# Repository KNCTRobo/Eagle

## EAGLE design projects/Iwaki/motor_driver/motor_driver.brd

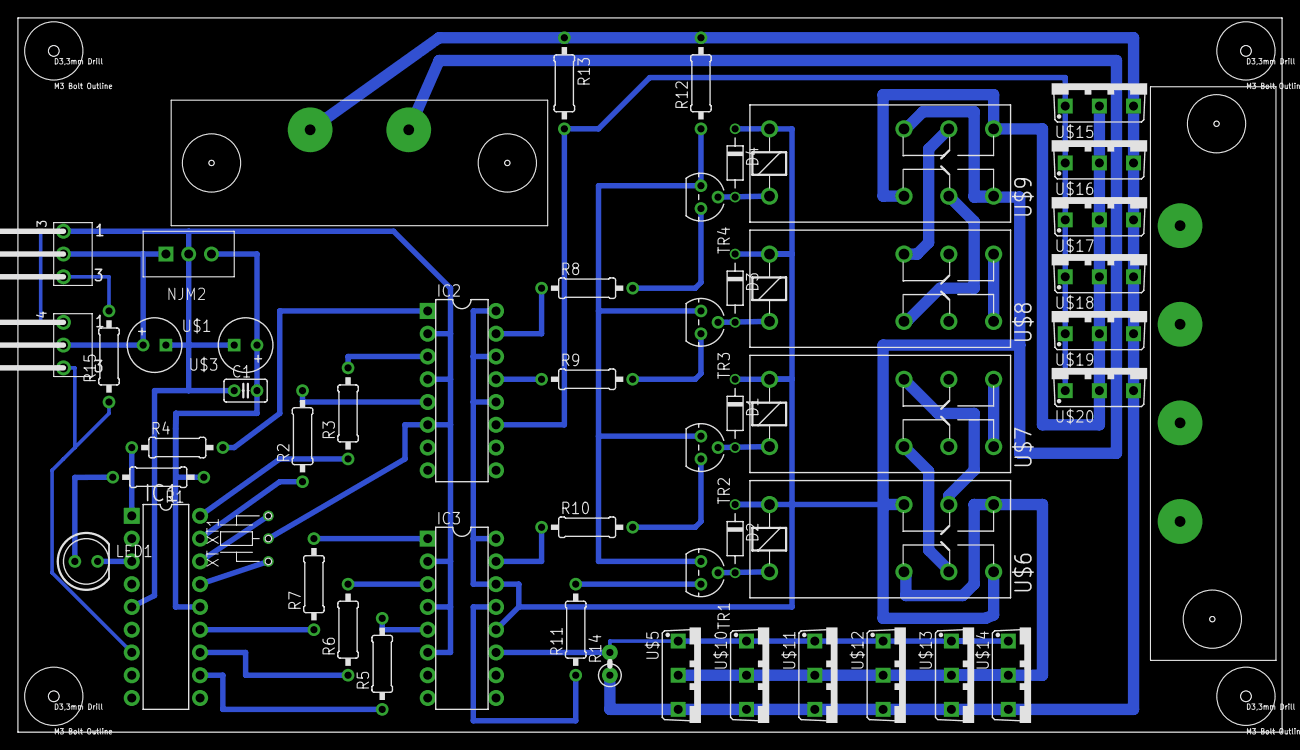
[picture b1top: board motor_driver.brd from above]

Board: 2 copper layers, 141.0 x 79.7 mm, 56 parts (0 on the bottom side), 50 nets.

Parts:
C1: C-2.54
D1, D2, D3, D4: DIODE7.5
H1, H2, H3, H4: HOLE3.3M3BOLT; HOLE3.3
IC1: PIC16F648; DIL18
IC2, IC3: TLP521; DIL16
J3, J4: 3PIN(L); 3PL
LED1: LED5MM
NJM2: NJM7805
R1: 2k; 0207/10
R2, R3, R4, R5, R6, R7, R8, R9, R10, R11: 10k; 0207/10
R12: 1; 0207/10
R13: 510; 0207/10
R14: 510; R0207V
R15: 0207/10
TR1, TR2, TR3, TR4: 2SC2001; TO92BCE
U$1, U$3: C-ELEC; C-6MM
U$2: BP341L
U$4: BP341L_1; BP341L
U$5, U$10, U$11, U$12, U$13, U$14, U$15, U$16, U$17, U$18, U$19, U$20: N-MOS; TO220BV
U$6, U$7, U$8, U$9: RELAY(L); G2R2
XT1: CERALOCK

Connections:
5V: C1.P$2, IC1.14, NJM2.OUT, R1.1, U$3.+
9V: J3.2, J4.2, NJM2.IN, U$1.+
12V: D1.PK, D2.PK, D3.PK, D4.PK, IC2.12, IC2.14, IC2.16, IC3.12, IC3.14, IC3.16, U$4.P$1, U$6.4, U$6.7, U$6.8, U$7.8, U$8.8, U$9.4, U$9.7, U$9.8
FET_D1: U$9.2, U$9.5, U$15.D, U$16.D, U$17.D, U$18.D, U$19.D, U$20.D
FET_G1: IC2.11, R13.2, U$15.G, U$16.G, U$17.G, U$18.G, U$19.G, U$20.G
FET_G2: IC3.11, R14.2, U$5.G, U$10.G, U$11.G, U$12.G, U$13.G, U$14.G
GND1: C1.P$1, IC1.5, IC2.2, IC2.4, IC2.6, IC3.2, IC3.4, IC3.6, J3.1, J4.1, NJM2.GND, U$1.-, U$3.-, XT1.P2
GND2: R12.2, R13.1, R14.1, U$4.P$2, U$5.S, U$10.S, U$11.S, U$12.S, U$13.S, U$14.S, U$15.S, U$16.S, U$17.S, U$18.S, U$19.S, U$20.S
GND3: R12.1, TR1.E, TR2.E, TR3.E, TR4.E
LED_A: LED1.A, R1.2
LED_C: IC1.3, LED1.K
unnamed: IC1.16, XT1.P3
unnamed: J3.3, R15.2
unnamed: IC1.15, XT1.P1
unnamed: IC1.17, R2.1
unnamed: IC1.18, R3.1
unnamed: IC1.1, R4.1
unnamed: IC1.13, R7.1
unnamed: IC1.12, R6.1
unnamed: IC1.11, R5.1
unnamed: IC2.5, R2.2
unnamed: IC2.3, R3.2
unnamed: IC2.1, R4.2
unnamed: IC3.1, R7.2
unnamed: IC3.3, R6.2
unnamed: IC3.5, R5.2
unnamed: IC2.15, R8.1
unnamed: IC2.13, R9.1
unnamed: IC3.15, R10.1
unnamed: IC3.13, R11.1
unnamed: R11.2, TR1.B
unnamed: D4.PA, TR4.C, U$9.1
unnamed: D3.PA, TR3.C, U$8.1
unnamed: D1.PA, TR2.C, U$7.1
unnamed: D2.PA, TR1.C, U$6.1
unnamed: U$2.P3, U$7.6
unnamed: U$5.D, U$6.2, U$6.5, U$10.D, U$11.D, U$12.D, U$13.D, U$14.D
unnamed: U$8.7, U$9.6
unnamed: U$8.2, U$9.3
unnamed: U$8.4, U$8.5
unnamed: R8.2, TR4.B
unnamed: R9.2, TR3.B
unnamed: R10.2, TR2.B
unnamed: U$2.P2, U$8.3
unnamed: U$2.P1, U$8.6
unnamed: U$2.P4, U$7.3
unnamed: U$6.6, U$7.7
unnamed: U$6.3, U$7.2
unnamed: U$7.4, U$7.5
SIGNAL: IC1.7, J4.3, R15.1

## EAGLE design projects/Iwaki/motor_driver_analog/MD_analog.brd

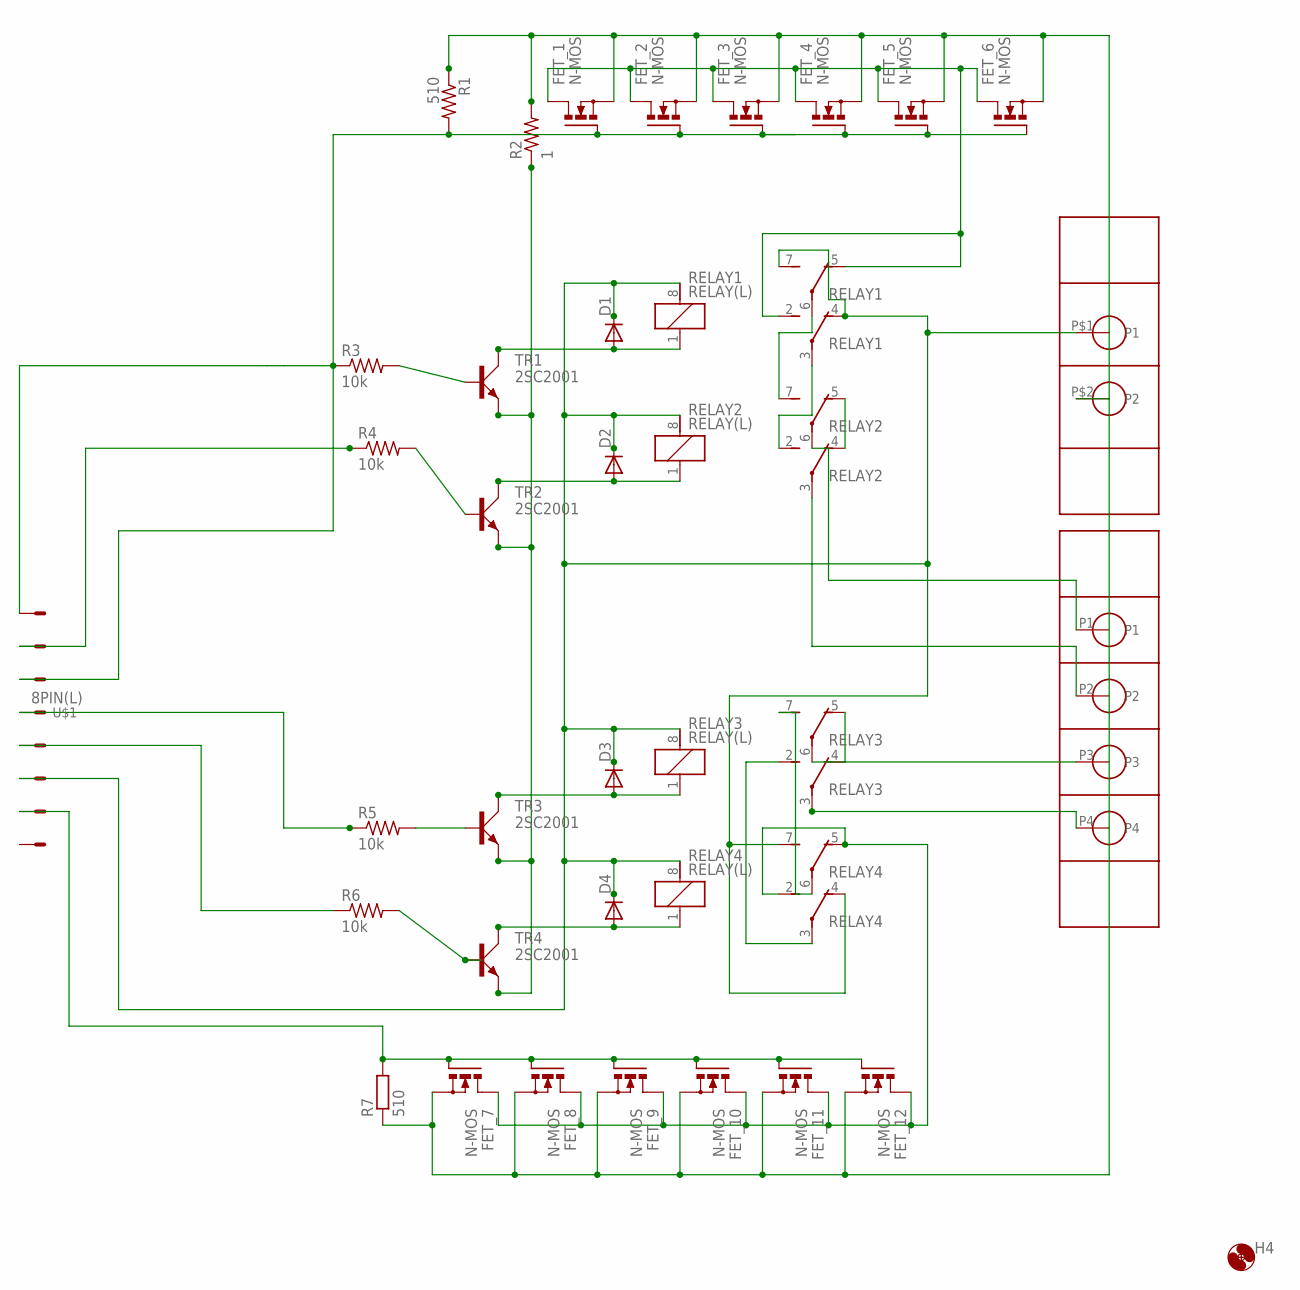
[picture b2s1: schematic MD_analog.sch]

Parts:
D1, D2, D3, D4: DIODE7.5
FET_1, FET_2, FET_3, FET_4, FET_5, FET_6, FET_7, FET_8, FET_9, FET_10, FET_11, FET_12: N-MOS; TO220BV
H4: HOLE3.3M3BOLT; HOLE3.3
R1: 510; 0207/10
R2: 1; 0207/10
R3, R4, R5, R6: 10k; 0207/10
R7: 510; R0207V
RELAY1, RELAY2, RELAY3, RELAY4: RELAY(L); G2R2
TR1, TR2, TR3, TR4: 2SC2001; TO92BCE
U$1: 8PIN(L); 8PL
U$2: BP341L
U$4: BP341L_1; BP341L

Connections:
12V: D1.PK (C), D2.PK (C), D3.PK (C), D4.PK (C), RELAY1.4 (O), RELAY1.7 (S), RELAY1.8 (2), RELAY2.8 (2), RELAY3.8 (2), RELAY4.4 (O), RELAY4.7 (S), RELAY4.8 (2), U$1.P3, U$4.P$1 (P1)
FET_G1: FET_1.G, FET_2.G, FET_3.G, FET_4.G, FET_5.G, FET_6.G, R1.2, U$1.P6
FET_G2: FET_7.G, FET_8.G, FET_9.G, FET_10.G, FET_11.G, FET_12.G, R7.2, U$1.P2
GND2: FET_1.S, FET_2.S, FET_3.S, FET_4.S, FET_5.S, FET_6.S, FET_7.S, FET_8.S, FET_9.S, FET_10.S, FET_11.S, FET_12.S, R1.1, R2.2, R7.1, U$4.P$2 (P2)
GND3: R2.1, TR1.E, TR2.E, TR3.E, TR4.E
MOS_D1: FET_7.D, FET_8.D, FET_9.D, FET_10.D, FET_11.D, FET_12.D, RELAY4.2 (S), RELAY4.5 (O)
MOS_D2: FET_1.D, FET_2.D, FET_3.D, FET_4.D, FET_5.D, FET_6.D, RELAY1.2 (S), RELAY1.5 (O)
unnamed: R3.1, U$1.P8
unnamed: R4.1, U$1.P7
unnamed: R5.1, U$1.P5
unnamed: R6.1, U$1.P4
unnamed: R6.2, TR4.B
unnamed: D1.PA (A), RELAY1.1, TR1.C
unnamed: D2.PA (A), RELAY2.1, TR2.C
unnamed: D3.PA (A), RELAY3.1, TR3.C
unnamed: D4.PA (A), RELAY4.1, TR4.C
unnamed: RELAY3.6, U$2.P3
unnamed: RELAY1.6, RELAY2.7 (S)
unnamed: RELAY1.3, RELAY2.2 (S)
unnamed: RELAY2.4 (O), RELAY2.5 (O)
unnamed: R3.2, TR1.B
unnamed: R4.2, TR2.B
unnamed: R5.2, TR3.B
unnamed: RELAY2.3, U$2.P2
unnamed: RELAY2.6, U$2.P1
unnamed: RELAY3.3, U$2.P4
unnamed: RELAY3.7 (S), RELAY4.6
unnamed: RELAY3.2 (S), RELAY4.3
unnamed: RELAY3.4 (O), RELAY3.5 (O)

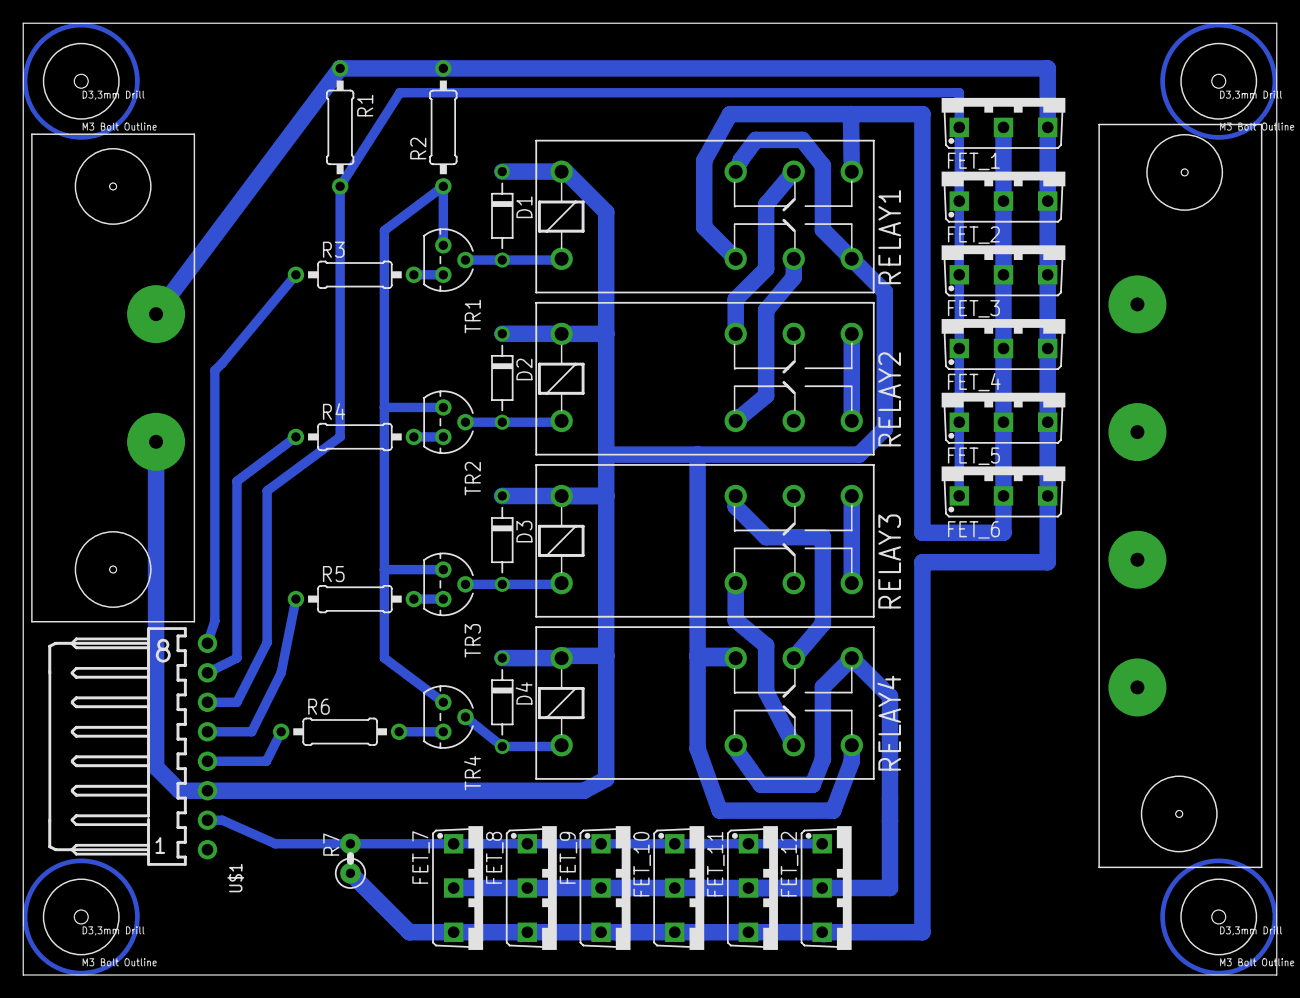
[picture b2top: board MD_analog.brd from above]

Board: 2 copper layers, 108.0 x 82.0 mm, 38 parts (0 on the bottom side), 29 nets.

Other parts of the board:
H1, H2, H3: HOLE3.3M3BOLT; HOLE3.3

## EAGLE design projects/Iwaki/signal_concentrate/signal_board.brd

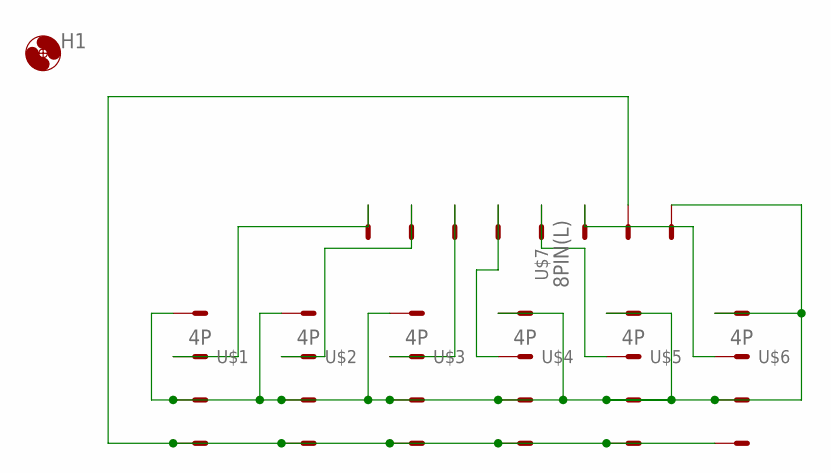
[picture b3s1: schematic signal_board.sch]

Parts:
H1: HOLE3.3M3BOLT; HOLE3.3
U$1, U$2, U$3, U$4, U$5, U$6: 4P
U$7: 8PIN(L); 8PL

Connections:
5V: U$1.P2, U$1.P4, U$2.P2, U$2.P4, U$3.P2, U$3.P4, U$4.P2, U$4.P4, U$5.P2, U$5.P4, U$6.P2, U$6.P4, U$7.P8
GND: U$1.P1, U$2.P1, U$3.P1, U$4.P1, U$5.P1, U$6.P1, U$7.P7
unnamed: U$5.P3, U$7.P5
unnamed: U$1.P3, U$7.P1
unnamed: U$2.P3, U$7.P2
unnamed: U$3.P3, U$7.P3
unnamed: U$4.P3, U$7.P4
unnamed: U$6.P3, U$7.P6

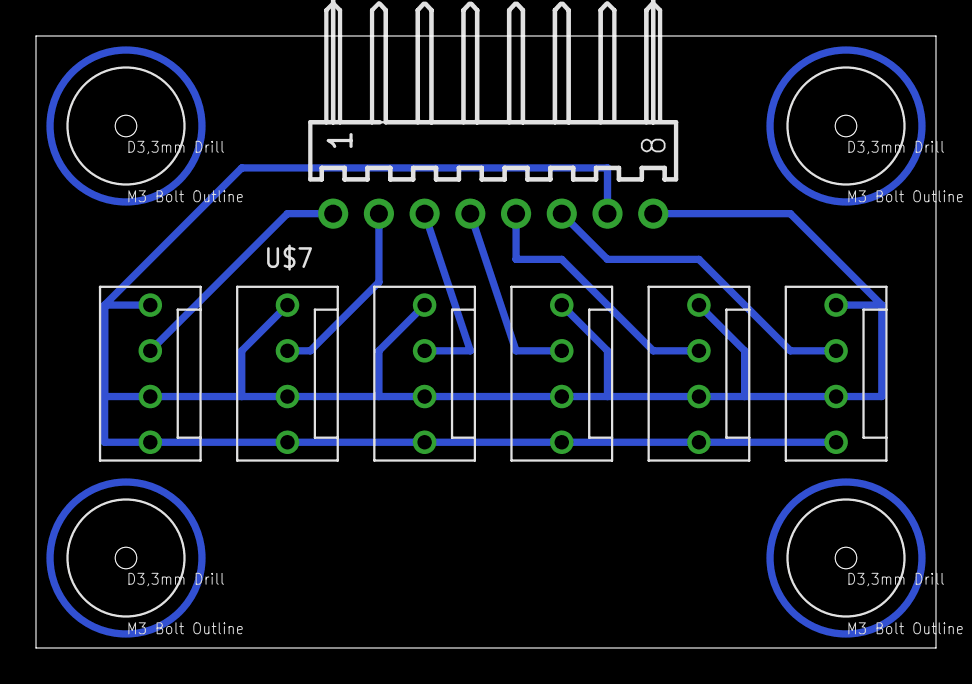
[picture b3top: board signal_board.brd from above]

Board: 2 copper layers, 50.0 x 34.0 mm, 11 parts (0 on the bottom side), 8 nets.

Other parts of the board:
H2, H3, H4: HOLE3.3M3BOLT; HOLE3.3

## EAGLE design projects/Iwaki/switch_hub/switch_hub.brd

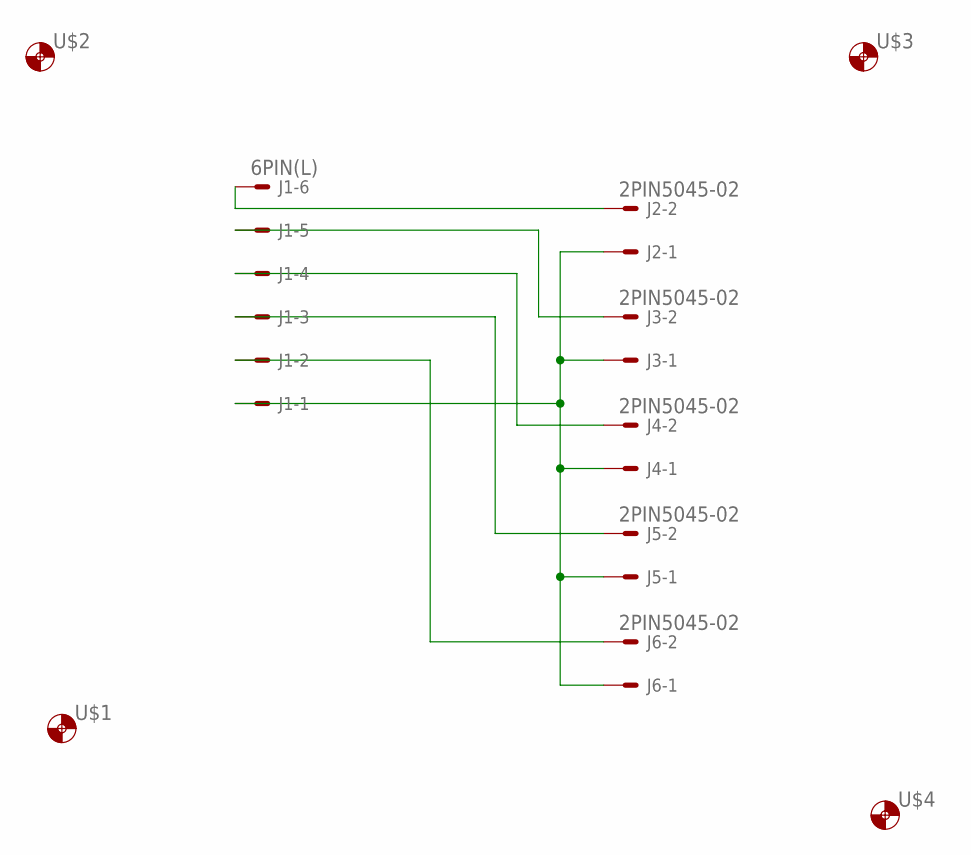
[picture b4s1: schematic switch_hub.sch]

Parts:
J1: 6PIN(L); 6PL
J2, J3, J4, J5, J6: 2PIN5045-02; 5045-02
U$1, U$2, U$3, U$4: 1MMDRILL; 1MDRILL

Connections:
unnamed: J1.1, J2.P$2, J3.P$2, J4.P$2, J5.P$2, J6.P$2
unnamed: J1.6, J2.P$1
unnamed: J1.5, J3.P$1
unnamed: J1.4, J4.P$1
unnamed: J1.3, J5.P$1
unnamed: J1.2, J6.P$1

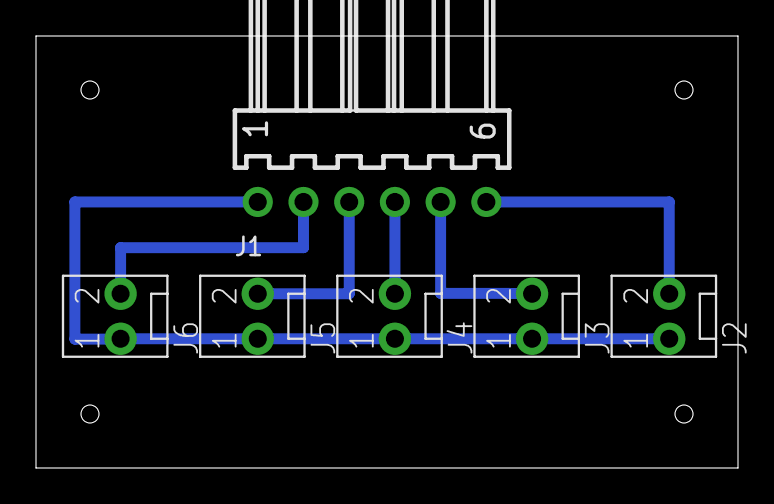
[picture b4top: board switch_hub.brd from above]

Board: 2 copper layers, 39.0 x 24.0 mm, 10 parts (0 on the bottom side), 6 nets.
